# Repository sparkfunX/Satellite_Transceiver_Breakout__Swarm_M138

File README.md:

# Satellite Transceiver Breakout - Swarm M138

[*SparkFun Satellite Transceiver Kit - Swarm M138*](https://www.sparkfun.com/products/21287)

A breakout for the Swarm M138 satellite transceiver.

This breakout allows you to power and communicate with the Swarm M138 using USB 3 or USB-C, or breakout pins.

We've written a Python3 PyQt5 GUI to let you communicate with the modem. You will find it in its own dedicated repo:
- [**SparkFun Swarm M138 GUI**](https://github.com/sparkfun/SparkFun_Swarm_M138_GUI)

You will find the modem manual in the [**Documents**](./Documents) folder. It contains the full list of modem commands and messages.

You can also integrate the satellite transceiver directly into your project; the breakout pads can be used to provide power and access the 3.3V UART TX and RX signals.

Open the two split jumper pads on the bottom of the PCB first, located between the TXO/CH340_RXI and RXI/CH340_TXO pads. Then connect:
* GND to GND on your Arduino board
* VIN to 5V/V_USB on your Arduino board
* TXO to RX on your Arduino board (3.3V only!)
* RXI to TX on your Arduino board (3.3V only!)

Our [Swarm Satellite Arduino Library](https://github.com/sparkfun/SparkFun_Swarm_Satellite_Arduino_Library) makes communicating with the modem really easy.

## Repository Contents

- [**/Hardware**](./Hardware) - contains the Eagle PCB, SCH and LBR design files
- [**/Documents**](./Documents) - contains the datasheet etc. for the Swarm M138
- [**LICENSE.md**](./LICENSE.md) - contains the licence information

<br>

- [**SparkFun Swarm M138 GUI**](https://github.com/sparkfun/SparkFun_Swarm_M138_GUI) - dedicated repo for the Swarm M138 GUI

## Product Versions

- [KIT-21287](https://www.sparkfun.com/products/21287) - SparkFun Satellite Transceiver Kit - Swarm M138
- [SPX-19236](https://www.sparkfun.com/products/19236) - Original SparkX version

## License Information

This product is _**open source**_!

Please review the LICENSE.md file for license information.

If you have any questions or concerns on licensing, please contact technical support on our [SparkFun forums](https://forum.sparkfun.com/viewforum.php?f=123).

Distributed as-is; no warranty is given.

- Your friends at SparkFun.

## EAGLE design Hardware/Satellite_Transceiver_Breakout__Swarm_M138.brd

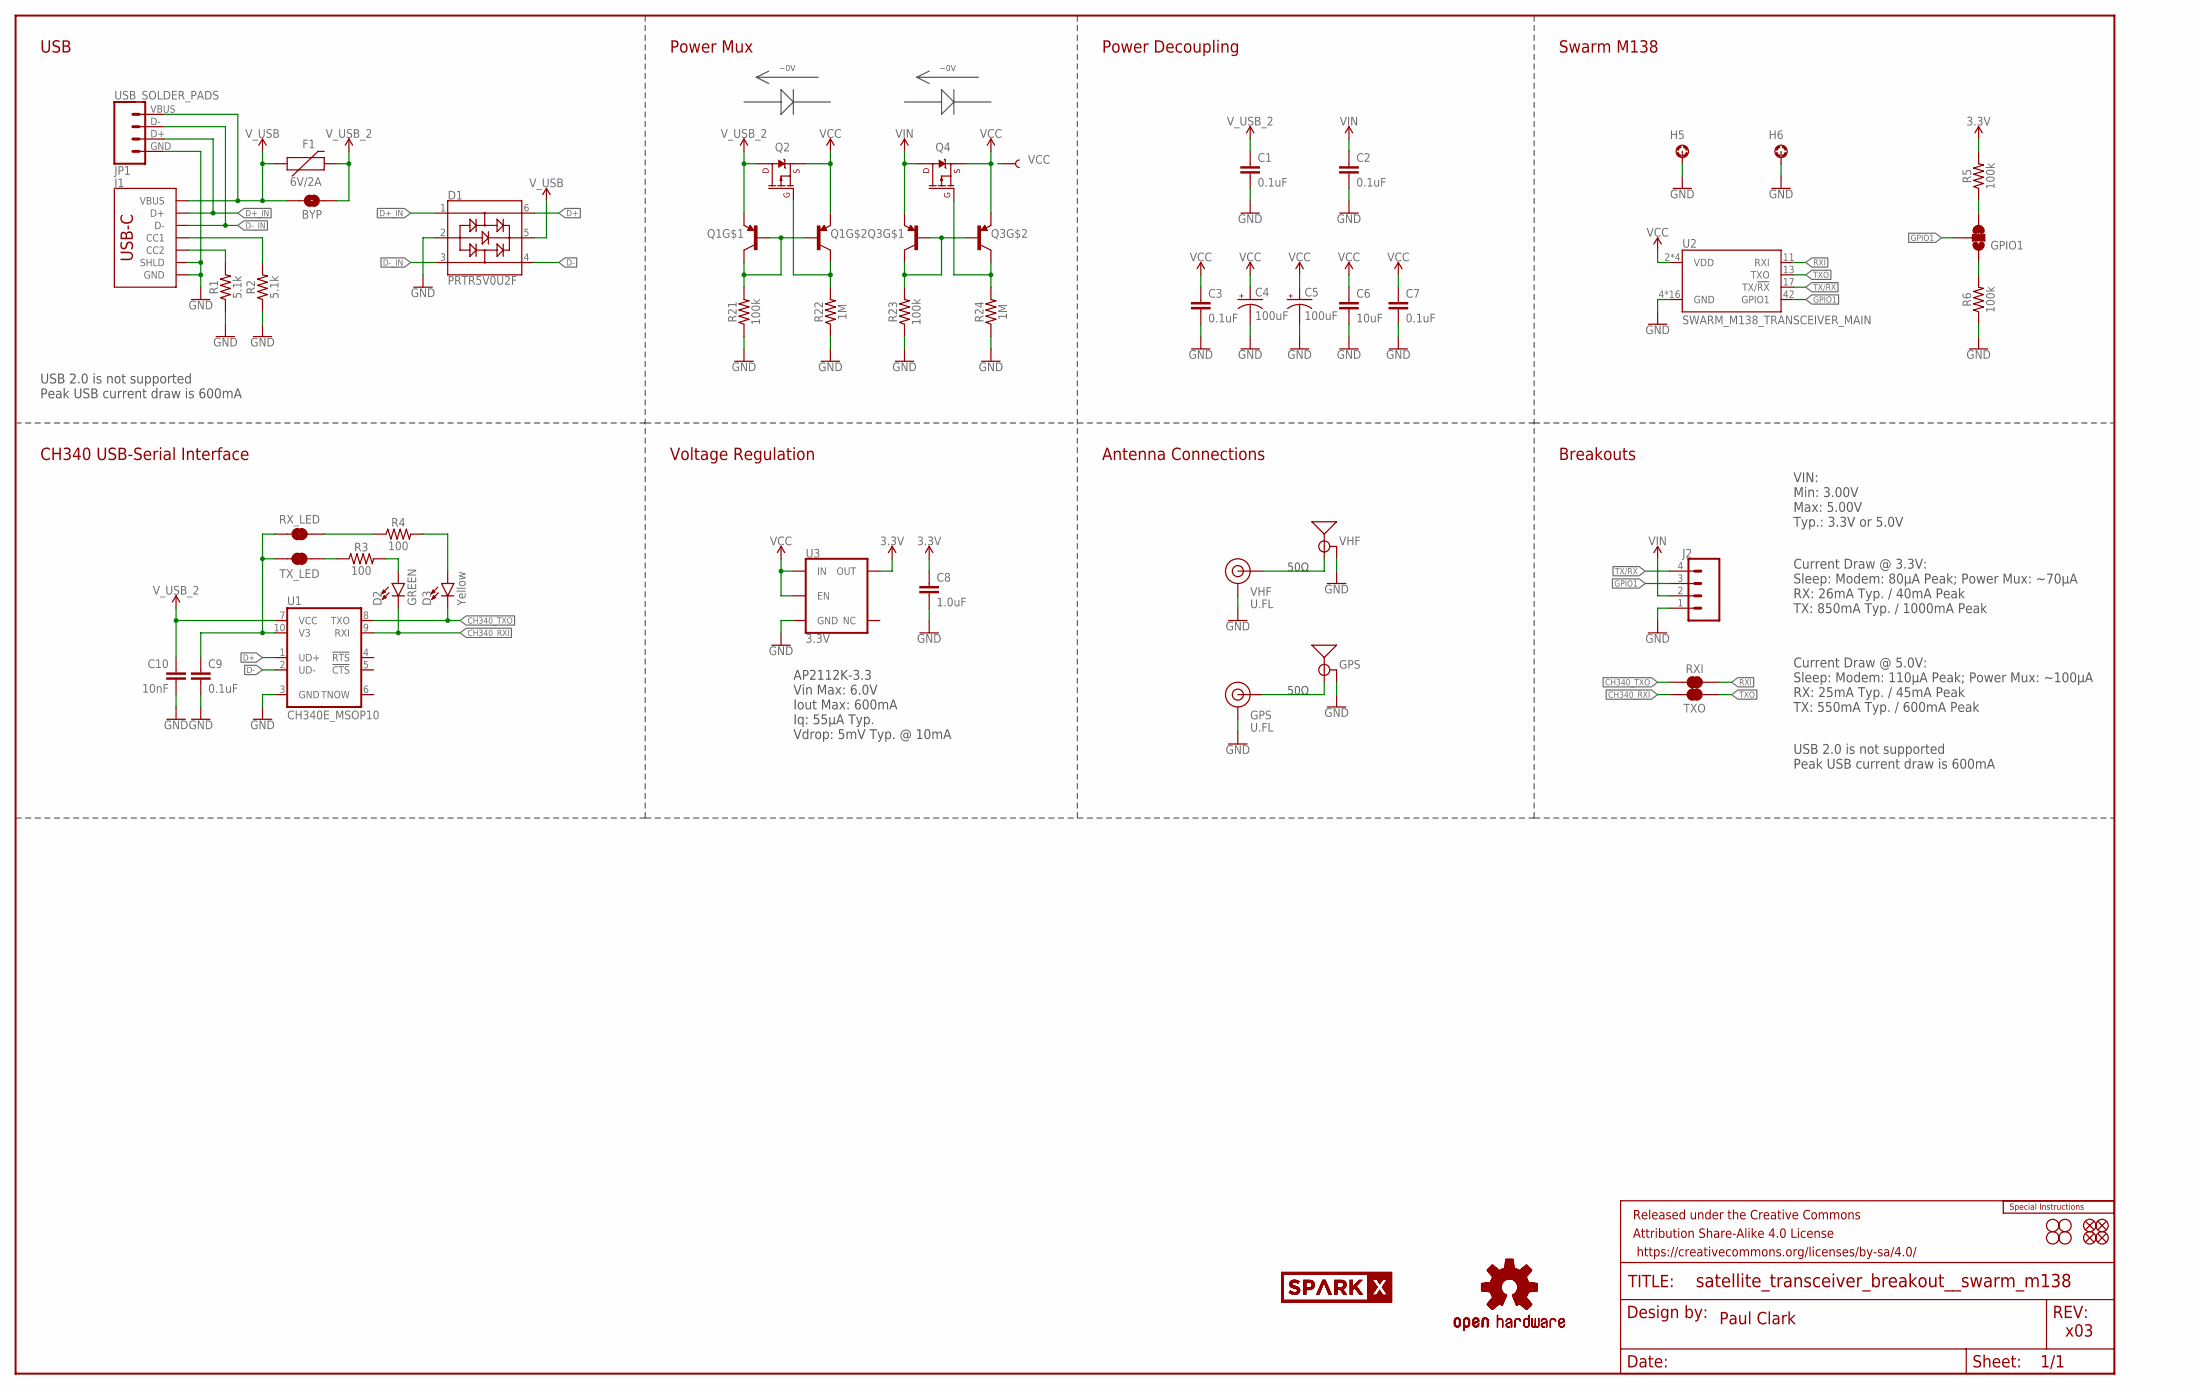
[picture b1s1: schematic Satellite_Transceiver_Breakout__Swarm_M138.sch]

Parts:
BYP: JUMPER-SMT_2_NO_SILK; SMT-JUMPER_2_NO_SILK
C1, C2, C3, C7, C9: 0.1uF; 0603
C4, C5: 100uF; PANASONIC_D
C6: 10uF; 0603
C8: 1.0uF; 0603
C10: 10nF; 0603
D1: PRTR5V0U2F; SOT886
D2: GREEN; LED-0603
D3: Yellow; LED-0603
E1: VHF; SMA-EDGE
E2: GPS; SMA-EDGE
F1: 6V/2A; 1210
FD1, FD2, FD3, FD4: FIDUCIAL1X2; FIDUCIAL-1X2
FRAME1: FRAME-LEDGER; CREATIVE_COMMONS
GPIO1: JUMPER-SMT_3_1-NC_TRACE_SILK; SMT-JUMPER_3_1-NC_TRACE_SILK
GPS: U.FL
H1, H2, H3, H4: STAND-OFF
H5, H6: STAND-OFF-REFLOW-M2.5_1.5MM_TALL; STAND-OFF-REFLOW-M2.5
J1: USB_C_2-LAYER_PADS; USB-C-16P-2LAYER-PADS
J2: CONN_041X04_NO_SILK; 1X04_NO_SILK
JP1: USB_SOLDER_PADS; USB-SOLDER-PADS
LOGO1: SPECIAL_INSTRUCTIONS-ORDERING; ORDERING_INSTRUCTIONS
LOGO2, LOGO3: OSHW-LOGOM; OSHW-LOGO-M
Q1, Q3: TRANS_PNP_DUALSOT-363; SOT363_PHILIPS
Q2, Q4: 20V/4.2A/52mΩ/1.4W; SOT23-3
R1, R2: 5.1k; 0603
R3, R4: 100; 0603
R5, R6, R21, R23: 100k; 0603
R22, R24: 1M; 0603
RXI: JUMPER-COMBO_2_NC_TRACE; COMBO-JUMPER_2_NC_TRACE
RX_LED: JUMPER-SMT_2_NC_TRACE_SILK; SMT-JUMPER_2_NC_TRACE_SILK
TXO: JUMPER-COMBO_2_NC_TRACE; COMBO-JUMPER_2_NC_TRACE
TX_LED: JUMPER-SMT_2_NC_TRACE_SILK; SMT-JUMPER_2_NC_TRACE_SILK
U1: CH340E_MSOP10; MSOP10
U2: SWARM_M138_TRANSCEIVER_MAIN; M.2-SWARM-M138-A
U3: 3.3V; SOT23-5
U$1, U$2: SPARKX-LOGO5; SPARKX-LARGE
VCC: TEST-POINT3X5; PAD.03X.05
VHF: U.FL

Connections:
3.3V: C8.1, R5.2, U3.5 (OUT)
CH340_RXI: D2.C, TXO.2, TXO.4 (2), U1.9 (RXI)
CH340_TXO: D3.C, RXI.1, RXI.3 (1), U1.8 (TXO)
D+: D1.6, U1.1 (UD+)
D+_IN: D1.1, J1.A6 (D+), J1.B6 (D+), JP1.D+ (3)
D-: D1.4, U1.2 (UD-)
D-_IN: D1.3, J1.A7 (D-), J1.B7 (D-), JP1.D- (2)
GND: C1.2, C2.2, C3.2, C4.-, C5.-, C6.2, C7.2, C8.2, C9.2, C10.2, D1.2, E1.GND@0 (GND), E1.GND@1 (GND), E1.GND@2 (GND), E1.GND@3 (GND), E2.GND@0 (GND), E2.GND@1 (GND), E2.GND@2 (GND), E2.GND@3 (GND), GPS.1 (GND), GPS.2 (GND), H5.1, H6.1, J1.GND, J1.GND2 (GND), J1.SHLD1 (SHLD), J1.SHLD2 (SHLD), J1.SHLD3 (SHLD), J1.SHLD4 (SHLD), J2.1, JP1.GND (4), R1.1, R2.1, R6.1, R21.1, R22.1, R23.1, R24.1, U1.3 (GND), U2.4 (GND), U2.9 (GND), U2.15 (GND), U2.18 (GND), U2.21 (GND), U2.26 (GND), U2.27 (GND), U2.29 (GND), U2.34 (GND), U2.35 (GND), U2.37 (GND), U2.40 (GND), U2.43 (GND), U2.50 (GND), U2.A1 (GND), U2.A2 (GND), U3.2 (GND), VHF.1 (GND), VHF.2 (GND)
GPIO1: GPIO1.2, J2.3, U2.42 (GPIO1)
GPS: E2.SIG (SIGNAL), GPS.FEED (SIGNAL)
unnamed: J1.B5 (CC2), R1.2
unnamed: J1.A5 (CC1), R2.2
unnamed: Q1.2 (B), Q1.5 (B), Q1.6 (C), R21.2
unnamed: C9.1, RX_LED.1, TX_LED.2, U1.10 (V3)
unnamed: R4.1, RX_LED.2
unnamed: D2.A, R3.2
unnamed: D3.A, R4.2
unnamed: R3.1, TX_LED.1
unnamed: Q1.3 (C), Q2.1 (G), R22.2
unnamed: GPIO1.3, R5.1
unnamed: Q3.2 (B), Q3.5 (B), Q3.6 (C), R23.2
unnamed: GPIO1.1, R6.2
unnamed: Q3.3 (C), Q4.1 (G), R24.2
RXI: RXI.2, RXI.4 (2), U2.11 (RXI)
TX/!RX!: J2.4, U2.17 (TX/!RX!)
TXO: TXO.1, TXO.3 (1), U2.13 (TXO)
VCC: C3.1, C4.+, C5.+, C6.1, C7.1, Q1.4 (E), Q2.2 (S), Q3.4 (E), Q4.2 (S), U2.2 (VDD), U2.39 (VDD), U2.41 (VDD), U2.52 (VDD), U3.1 (IN), U3.3 (EN), VCC.1
VHF: E1.SIG (SIGNAL), VHF.FEED (SIGNAL)
VIN: C2.1, J2.2, Q3.1 (E), Q4.3 (D)
V_USB: BYP.2, D1.5, F1.1, J1.VBUS1 (VBUS), J1.VBUS2 (VBUS), JP1.VBUS (1)
V_USB_2: BYP.1, C1.1, C10.1, F1.2, Q1.1 (E), Q2.3 (D), U1.7 (VCC)

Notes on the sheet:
x03
Paul Clark
USB
Power Mux
~0V
Power Decoupling
CH340 USB-Serial Interface
Swarm M138
Antenna Connections
50Ω
Breakouts
VIN: Min: 3.00V Max: 5.00V Typ.: 3.3V or 5.0V
Current Draw @ 3.3V: Sleep: Modem: 80µA Peak; Power Mux: ~70µA RX: 26mA Typ. / 40mA Peak TX: 850mA Typ. / 1000mA Peak
Current Draw @ 5.0V: Sleep: Modem: 110µA Peak; Power Mux: ~100µA RX: 25mA Typ. / 45mA Peak TX: 550mA Typ. / 600mA Peak
USB 2.0 is not supported Peak USB current draw is 600mA
Voltage Regulation
AP2112K-3.3 Vin Max: 6.0V Iout Max: 600mA Iq: 55µA Typ. Vdrop: 5mV Typ. @ 10mA

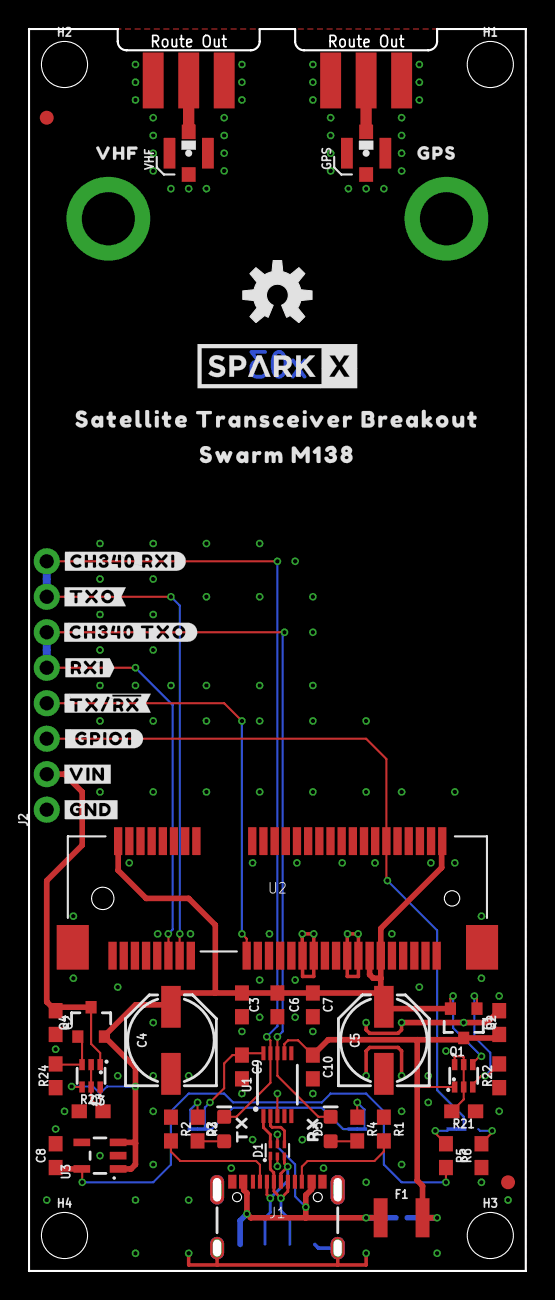
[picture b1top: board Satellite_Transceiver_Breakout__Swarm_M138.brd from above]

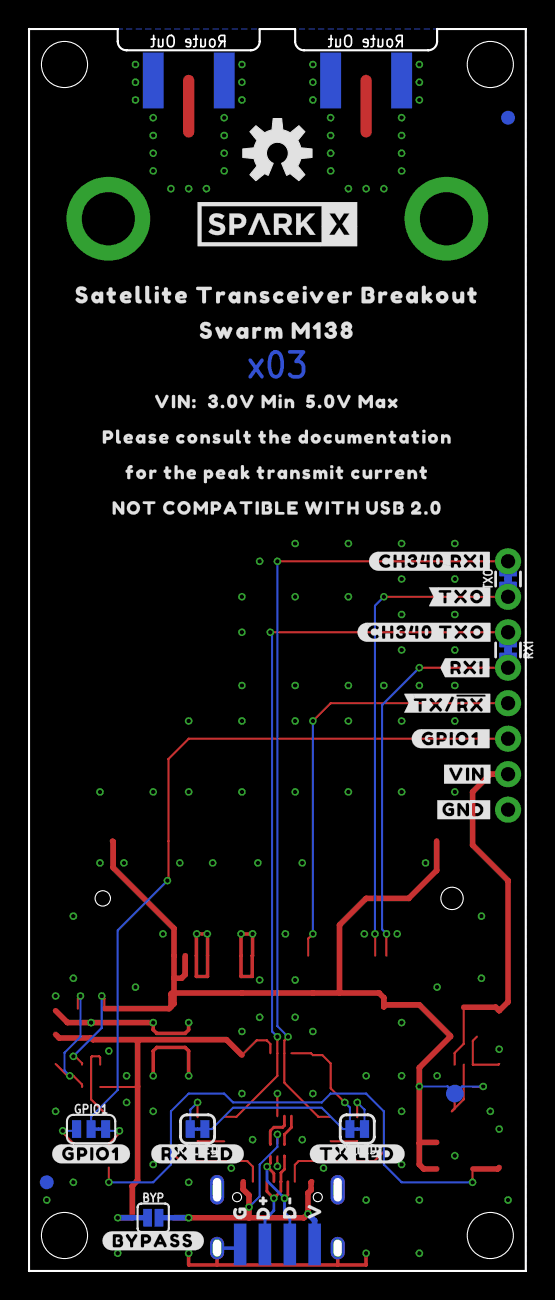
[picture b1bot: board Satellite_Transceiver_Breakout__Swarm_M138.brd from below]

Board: 2 copper layers, 35.1 x 88.5 mm, 97 parts (34 on the bottom side), 31 nets.

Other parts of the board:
U$3: VHF0
U$4: GPS0
U$5: VIN#__3#0V_MIN__5#0V_MAX0
U$6: PLEASE_CONSULT_THE_DOCUMENTATION0
U$7: #CH340_RXI#0
U$8: #CH340_RXI#341
U$9: #TXO#341
U$10: #TXO#342
U$11: #CH340_TXO#0
U$12: #CH340_TXO#341
U$13: #RXI#0
U$14: #RXI#1
U$15: #TX##RX##1
U$16: #TX##RX##0
U$17: #GPIO1_#2
U$18: V0
U$19: #GPIO1#0
U$20: #_GPIO1#2
U$21, U$22: #VIN#0
U$23, U$24: #GND#0
U$25: TX0
U$26: RX0
U$27: #TX_LED#0
U$28: #RX_LED#0
U$29: #BYPASS#0
U$30: G3
U$31: FOR_THE_PEAK_TRANSMIT_CURRENT1
U$32: NOT_COMPATIBLE_WITH_USB_2#02
U$34, U$39: SATELLITE_TRANSCEIVER_BREAKOUT0
U$36: D#2
U$37: D#1
U$40, U$41: SWARM_M1381

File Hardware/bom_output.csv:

Qty, PROD_ID, Names, Value, Package
5, CAP-08604, C1; C2; C3; C7; C9, 0.1uF, 0603
2, CAP-12547, C4; C5, 100uF, PANASONIC_D
1, CAP-11015, C6, 10uF, 0603
1, CAP-13930, C8, 1.0uF, 0603
1, CAP-00867, C10, 10nF, 0603
1, DIO-14084, D1, PRTR5V0U2F, SOT886
1, DIO-00821, D2, GREEN, LED-0603
1, DIO-09003, D3, Yellow, LED-0603
1, CONN-08289, E1, VHF, SMA-EDGE
1, CONN-08289, E2, GPS, SMA-EDGE
1, RES-14313, F1, 6V/2A, 1210
2, CONN-09193, GPS; VHF, U.FL, U.FL
2, HW-16629, H5; H6, STAND-OFF-REFLOW-M2.5_1.5MM_TALL, STAND-OFF-REFLOW-M2.5
1, CONN-14122, J1, , USB-C-16P-2LAYER-PADS
1, CONN-09696, J2, , 1X04_NO_SILK
2, TRANS-14386, Q1; Q3, , SOT363_PHILIPS
2, TRANS-14388, Q2; Q4, 20V/4.2A/52mΩ/1.4W, SOT23-3
2, RES-12083, R1; R2, 5.1k, 0603
2, RES-07863, R3; R4, 100, 0603
4, RES-07828, R5; R6; R21; R23, 100k, 0603
2, RES-07868, R22; R24, 1M, 0603
1, IC-14135, U1, CH340E_MSOP10, MSOP10
1, CONN-16558, U2, SWARM_M138_TRANSCEIVER_MAIN, M.2-SWARM-M138-A
1, VREG-12457, U3, 3.3V, SOT23-5

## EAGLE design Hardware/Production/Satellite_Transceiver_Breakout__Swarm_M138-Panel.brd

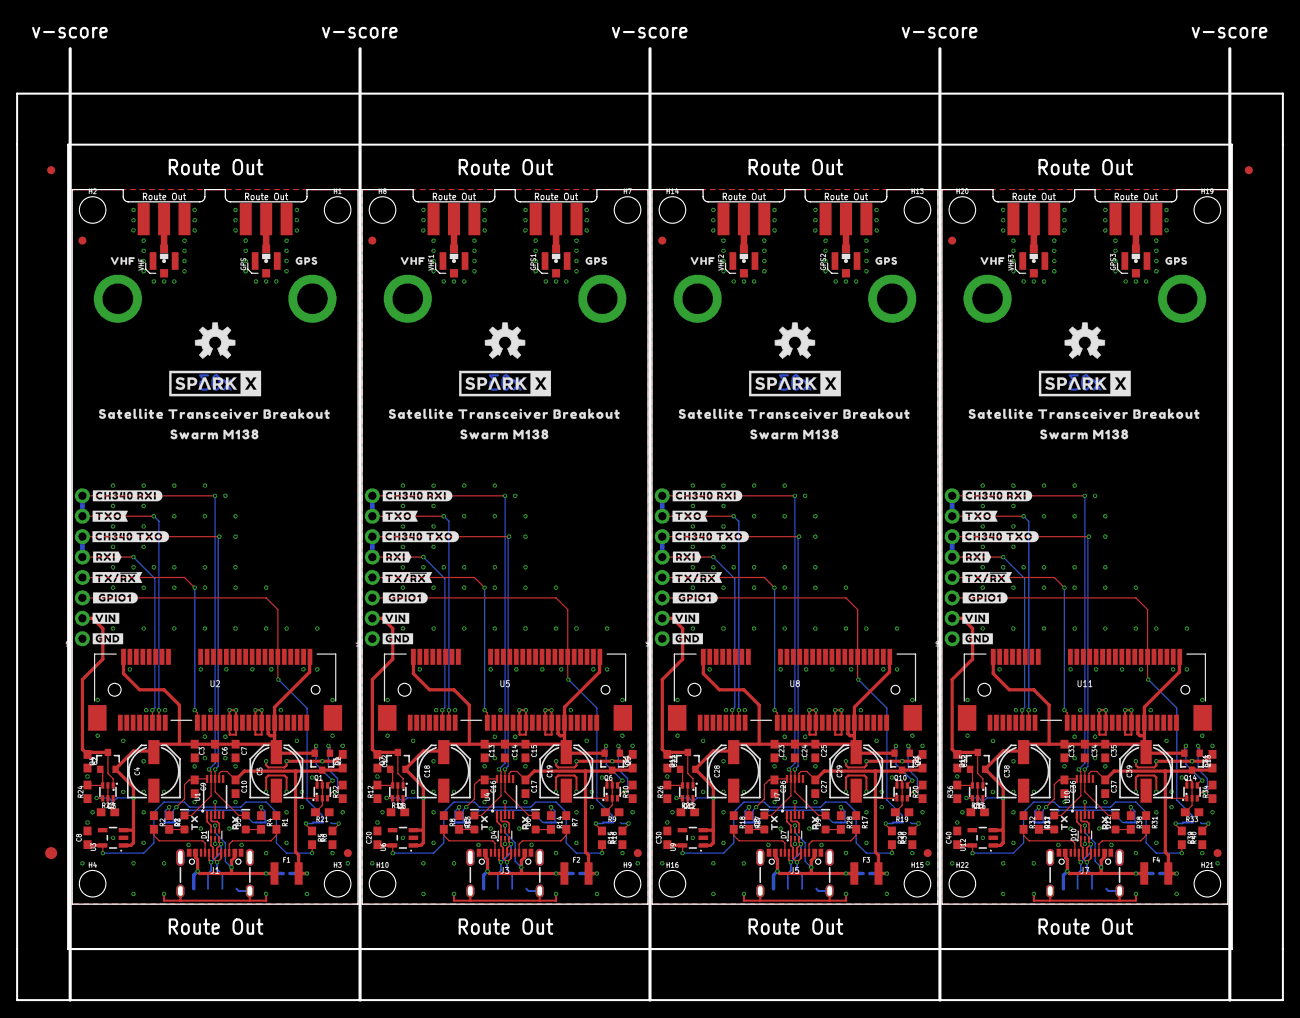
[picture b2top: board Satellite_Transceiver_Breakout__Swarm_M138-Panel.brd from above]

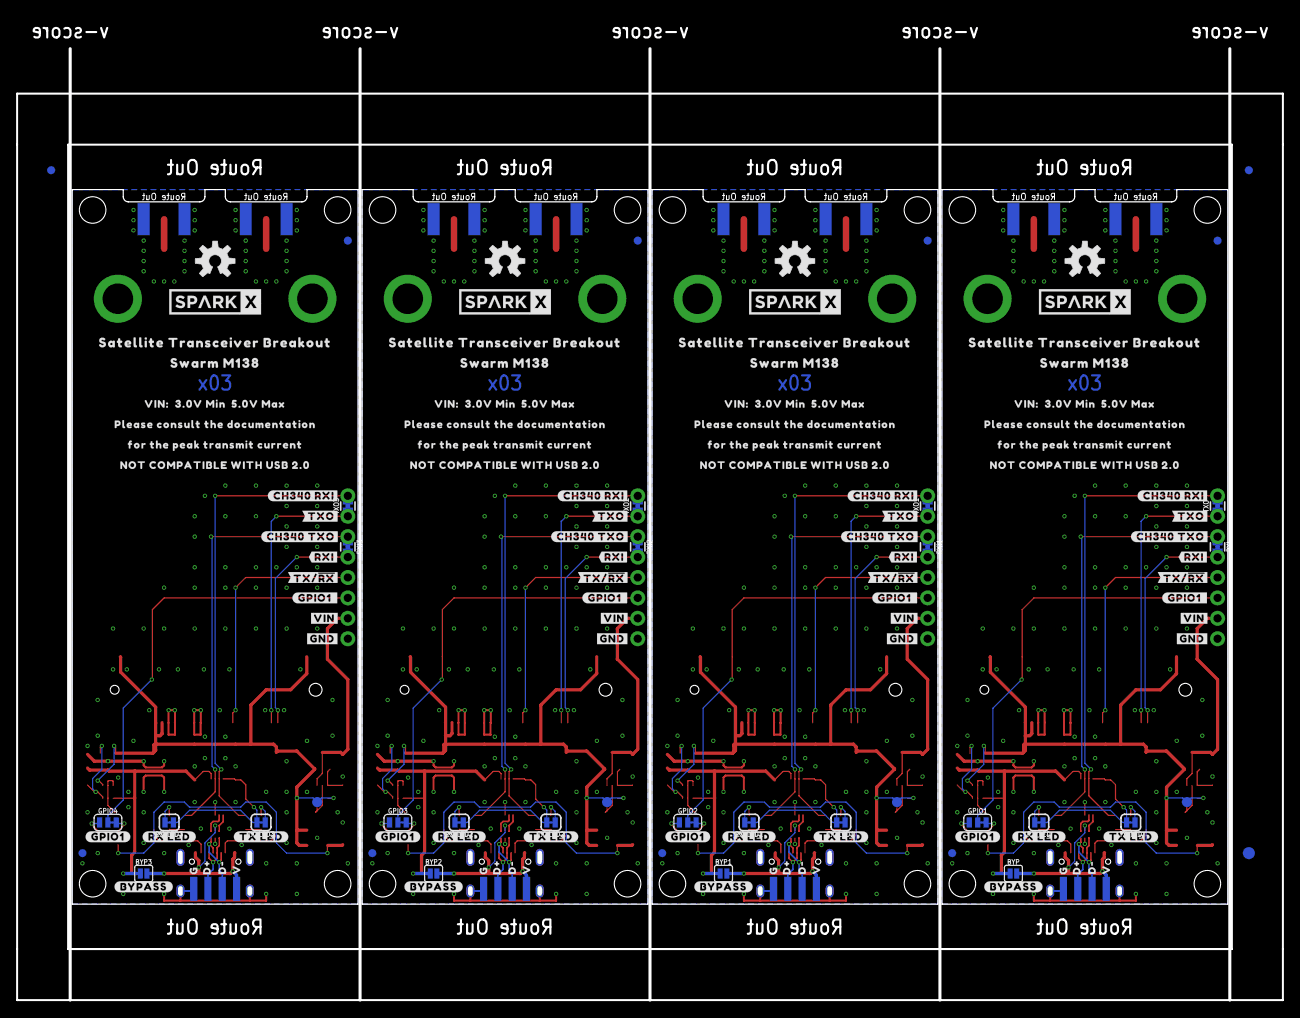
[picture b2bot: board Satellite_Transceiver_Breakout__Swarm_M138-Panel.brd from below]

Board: 2 copper layers, 157.1 x 122.0 mm, 386 parts (139 on the bottom side), 124 nets.

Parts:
BYP, BYP1, BYP2, BYP3: JUMPER-SMT_2_NO_SILK; SMT-JUMPER_2_NO_SILK
C1, C2, C3, C7, C9, C11, C12, C13, C15, C16, C21, C22, C23, C25, C26, C31, C32, C33, C35, C36: 0.1uF; 0603
C4, C5, C18, C19, C28, C29, C38, C39: 100uF; PANASONIC_D
C6, C14, C24, C34: 10uF; 0603
C8, C20, C30, C40: 1.0uF; 0603
C10, C17, C27, C37: 10nF; 0603
D1, D4, D7, D10: PRTR5V0U2F; SOT886
D2, D5, D8, D11: GREEN; LED-0603
D3, D6, D9, D12: Yellow; LED-0603
E1, E3, E5, E7: VHF; SMA-EDGE
E2, E4, E6, E8: GPS; SMA-EDGE
E$1, E$2, E$3, E$4: FIDUCIAL-1X2
E$5, E$6: FIDUCIAL-1.5X3
F1, F2, F3, F4: 6V/2A; 1210
FD1, FD2, FD3, FD4, FD5, FD6, FD7, FD8, FD9, FD10, FD11, FD12, FD13, FD14, FD15, FD16: FIDUCIAL1X2; FIDUCIAL-1X2
GPIO1, GPIO2, GPIO3, GPIO4: JUMPER-SMT_3_1-NC_TRACE_SILK; SMT-JUMPER_3_1-NC_TRACE_SILK
GPS, GPS1, GPS2, GPS3: U.FL
H1, H2, H3, H4, H7, H8, H9, H10, H13, H14, H15, H16, H19, H20, H21, H22: STAND-OFF
H5, H6, H11, H12, H17, H18, H23, H24: STAND-OFF-REFLOW-M2.5_1.5MM_TALL; STAND-OFF-REFLOW-M2.5
J1, J3, J5, J7: USB-C-16P-2LAYER-PADS
J2, J4, J6, J8: 1X04_NO_SILK
JP1, JP2, JP3, JP4: USB_SOLDER_PADS; USB-SOLDER-PADS
LOGO1, LOGO2, LOGO3, LOGO4, LOGO5, LOGO6, LOGO7, LOGO8: OSHW-LOGOM; OSHW-LOGO-M
Q1, Q3, Q6, Q8, Q10, Q12, Q14, Q16: SOT363_PHILIPS
Q2, Q4, Q5, Q7, Q9, Q11, Q13, Q15: 20V/4.2A/52mΩ/1.4W; SOT23-3
R1, R2, R7, R8, R17, R18, R31, R32: 5.1k; 0603
R3, R4, R13, R14, R27, R28, R37, R38: 100; 0603
R5, R6, R9, R11, R15, R16, R19, R21, R23, R25, R29, R30, R33, R35, R39, R40: 100k; 0603
R10, R12, R20, R22, R24, R26, R34, R36: 1M; 0603
RXI, RXI1, RXI2, RXI3: JUMPER-COMBO_2_NC_TRACE; COMBO-JUMPER_2_NC_TRACE
RX_LED, RX_LED1, RX_LED2, RX_LED3: JUMPER-SMT_2_NC_TRACE_SILK; SMT-JUMPER_2_NC_TRACE_SILK
TXO, TXO1, TXO2, TXO3: JUMPER-COMBO_2_NC_TRACE; COMBO-JUMPER_2_NC_TRACE
TX_LED, TX_LED1, TX_LED2, TX_LED3: JUMPER-SMT_2_NC_TRACE_SILK; SMT-JUMPER_2_NC_TRACE_SILK
U1, U4, U7, U10: CH340E_MSOP10; MSOP10
U2, U5, U8, U11: SWARM_M138_TRANSCEIVER_MAIN; M.2-SWARM-M138-A
U3, U6, U9, U12: 3.3V; SOT23-5
U$1, U$2, U$33, U$35, U$77, U$78, U$115, U$116: SPARKX-LOGO5; SPARKX-LARGE
U$3, U$38, U$79, U$117: VHF0
U$4, U$42, U$80, U$118: GPS0
U$5, U$76, U$114, U$152: VIN#__3#0V_MIN__5#0V_MAX0
U$6, U$73, U$111, U$149: PLEASE_CONSULT_THE_DOCUMENTATION0
U$7, U$52, U$90, U$128: #CH340_RXI#0
U$8, U$53, U$91, U$129: #CH340_RXI#341
U$9, U$54, U$92, U$130: #TXO#341
U$10, U$55, U$93, U$131: #TXO#342
U$11, U$56, U$94, U$132: #CH340_TXO#0
U$12, U$57, U$95, U$133: #CH340_TXO#341
U$13, U$58, U$96, U$134: #RXI#0
U$14, U$59, U$97, U$135: #RXI#1
U$15, U$61, U$99, U$137: #TX##RX##1
U$16, U$60, U$98, U$136: #TX##RX##0
U$17, U$63, U$101, U$139: #GPIO1_#2
U$18, U$65, U$103, U$141: V0
U$19, U$62, U$100, U$138: #GPIO1#0
U$20, U$64, U$102, U$140: #_GPIO1#2
U$21, U$22, U$43, U$44, U$81, U$82, U$119, U$120: #VIN#0
U$23, U$24, U$45, U$46, U$83, U$84, U$121, U$122: #GND#0
U$25, U$47, U$85, U$123: TX0
U$26, U$48, U$86, U$124: RX0
U$27, U$49, U$87, U$125: #TX_LED#0
U$28, U$50, U$88, U$126: #RX_LED#0
U$29, U$51, U$89, U$127: #BYPASS#0
U$30, U$66, U$104, U$142: G3
U$31, U$74, U$112, U$150: FOR_THE_PEAK_TRANSMIT_CURRENT1
U$32, U$75, U$113, U$151: NOT_COMPATIBLE_WITH_USB_2#02
U$34, U$39, U$69, U$70, U$107, U$108, U$145, U$146: SATELLITE_TRANSCEIVER_BREAKOUT0
U$36, U$67, U$105, U$143: D#2
U$37, U$68, U$106, U$144: D#1
U$40, U$41, U$71, U$72, U$109, U$110, U$147, U$148: SWARM_M1381
VCC, VCC1, VCC2, VCC3: TEST-POINT3X5; PAD.03X.05
VHF, VHF1, VHF2, VHF3: U.FL

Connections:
3.3V: C8.1, R5.2, U3.5
3.3V1: C20.1, R15.2, U6.5
3.3V2: C30.1, R29.2, U9.5
3.3V3: C40.1, R39.2, U12.5
CH340_RXI: D2.C, TXO.2, TXO.4, U1.9
CH340_RXI1: D5.C, TXO1.2, TXO1.4, U4.9
CH340_RXI2: D8.C, TXO2.2, TXO2.4, U7.9
CH340_RXI3: D11.C, TXO3.2, TXO3.4, U10.9
CH340_TXO: D3.C, RXI.1, RXI.3, U1.8
CH340_TXO1: D6.C, RXI1.1, RXI1.3, U4.8
CH340_TXO2: D9.C, RXI2.1, RXI2.3, U7.8
CH340_TXO3: D12.C, RXI3.1, RXI3.3, U10.8
D+: D1.6, U1.1
D+1: D4.6, U4.1
D+2: D7.6, U7.1
D+3: D10.6, U10.1
D+_IN: D1.1, J1.A6, J1.B6, JP1.D+
D+_IN1: D4.1, J3.A6, J3.B6, JP2.D+
D+_IN2: D7.1, J5.A6, J5.B6, JP3.D+
D+_IN3: D10.1, J7.A6, J7.B6, JP4.D+
D-: D1.4, U1.2
D-1: D4.4, U4.2
D-2: D7.4, U7.2
D-3: D10.4, U10.2
D-_IN: D1.3, J1.A7, J1.B7, JP1.D-
D-_IN1: D4.3, J3.A7, J3.B7, JP2.D-
D-_IN2: D7.3, J5.A7, J5.B7, JP3.D-
D-_IN3: D10.3, J7.A7, J7.B7, JP4.D-
GND: C1.2, C2.2, C3.2, C4.-, C5.-, C6.2, C7.2, C8.2, C9.2, C10.2, D1.2, E1.GND@0, E1.GND@1, E1.GND@2, E1.GND@3, E2.GND@0, E2.GND@1, E2.GND@2, E2.GND@3, GPS.1, GPS.2, H5.1, H6.1, J1.GND, J1.GND2, J1.SHLD1, J1.SHLD2, J1.SHLD3, J1.SHLD4, J2.1, JP1.GND, R1.1, R2.1, R6.1, R21.1, R22.1, R23.1, R24.1, U1.3, U2.4, U2.9, U2.15, U2.18, U2.21, U2.26, U2.27, U2.29, U2.34, U2.35, U2.37, U2.40, U2.43, U2.50, U2.A1, U2.A2, U3.2, VHF.1, VHF.2
GND1: C11.2, C12.2, C13.2, C14.2, C15.2, C16.2, C17.2, C18.-, C19.-, C20.2, D4.2, E3.GND@0, E3.GND@1, E3.GND@2, E3.GND@3, E4.GND@0, E4.GND@1, E4.GND@2, E4.GND@3, GPS1.1, GPS1.2, H11.1, H12.1, J3.GND, J3.GND2, J3.SHLD1, J3.SHLD2, J3.SHLD3, J3.SHLD4, J4.1, JP2.GND, R7.1, R8.1, R9.1, R10.1, R11.1, R12.1, R16.1, U4.3, U5.4, U5.9, U5.15, U5.18, U5.21, U5.26, U5.27, U5.29, U5.34, U5.35, U5.37, U5.40, U5.43, U5.50, U5.A1, U5.A2, U6.2, VHF1.1, VHF1.2
GND2: C21.2, C22.2, C23.2, C24.2, C25.2, C26.2, C27.2, C28.-, C29.-, C30.2, D7.2, E5.GND@0, E5.GND@1, E5.GND@2, E5.GND@3, E6.GND@0, E6.GND@1, E6.GND@2, E6.GND@3, GPS2.1, GPS2.2, H17.1, H18.1, J5.GND, J5.GND2, J5.SHLD1, J5.SHLD2, J5.SHLD3, J5.SHLD4, J6.1, JP3.GND, R17.1, R18.1, R19.1, R20.1, R25.1, R26.1, R30.1, U7.3, U8.4, U8.9, U8.15, U8.18, U8.21, U8.26, U8.27, U8.29, U8.34, U8.35, U8.37, U8.40, U8.43, U8.50, U8.A1, U8.A2, U9.2, VHF2.1, VHF2.2
GND3: C31.2, C32.2, C33.2, C34.2, C35.2, C36.2, C37.2, C38.-, C39.-, C40.2, D10.2, E7.GND@0, E7.GND@1, E7.GND@2, E7.GND@3, E8.GND@0, E8.GND@1, E8.GND@2, E8.GND@3, GPS3.1, GPS3.2, H23.1, H24.1, J7.GND, J7.GND2, J7.SHLD1, J7.SHLD2, J7.SHLD3, J7.SHLD4, J8.1, JP4.GND, R31.1, R32.1, R33.1, R34.1, R35.1, R36.1, R40.1, U10.3, U11.4, U11.9, U11.15, U11.18, U11.21, U11.26, U11.27, U11.29, U11.34, U11.35, U11.37, U11.40, U11.43, U11.50, U11.A1, U11.A2, U12.2, VHF3.1, VHF3.2
GPIO1: GPIO1.2, J2.3, U2.42
GPIO2: GPIO2.2, J4.3, U5.42
GPIO3: GPIO3.2, J6.3, U8.42
GPIO4: GPIO4.2, J8.3, U11.42
GPS: E2.SIG, GPS.FEED
GPS1: E4.SIG, GPS1.FEED
GPS2: E6.SIG, GPS2.FEED
GPS3: E8.SIG, GPS3.FEED
unnamed: J3.B5, R7.2
unnamed: J1.B5, R1.2
unnamed: J1.A5, R2.2
unnamed: J3.A5, R8.2
unnamed: Q1.2, Q1.5, Q1.6, R21.2
unnamed: C9.1, RX_LED.1, TX_LED.2, U1.10
unnamed: R4.1, RX_LED.2
unnamed: Q6.2, Q6.5, Q6.6, R9.2
unnamed: D2.A, R3.2
unnamed: D3.A, R4.2
unnamed: Q5.1, Q6.3, R10.2
unnamed: R3.1, TX_LED.1
unnamed: Q1.3, Q2.1, R22.2
unnamed: GPIO1.3, R5.1
unnamed: Q3.2, Q3.5, Q3.6, R23.2
unnamed: GPIO1.1, R6.2
unnamed: Q8.2, Q8.5, Q8.6, R11.2
unnamed: Q7.1, Q8.3, R12.2
unnamed: C16.1, RX_LED1.1, TX_LED1.2, U4.10
unnamed: D5.A, R13.2
unnamed: D6.A, R14.2
unnamed: R14.1, RX_LED1.2
unnamed: R13.1, TX_LED1.1
unnamed: GPIO2.3, R15.1
unnamed: GPIO2.1, R16.2
unnamed: J5.B5, R17.2
unnamed: J5.A5, R18.2
unnamed: Q3.3, Q4.1, R24.2
unnamed: Q10.2, Q10.5, Q10.6, R19.2
unnamed: Q9.1, Q10.3, R20.2
unnamed: Q12.2, Q12.5, Q12.6, R25.2
unnamed: Q11.1, Q12.3, R26.2
unnamed: C26.1, RX_LED2.1, TX_LED2.2, U7.10
unnamed: D8.A, R27.2
unnamed: D9.A, R28.2
unnamed: R28.1, RX_LED2.2
unnamed: R27.1, TX_LED2.1
unnamed: GPIO3.3, R29.1
unnamed: GPIO3.1, R30.2
unnamed: J7.B5, R31.2
unnamed: J7.A5, R32.2
unnamed: Q14.2, Q14.5, Q14.6, R33.2
unnamed: Q13.1, Q14.3, R34.2
unnamed: Q16.2, Q16.5, Q16.6, R35.2
unnamed: Q15.1, Q16.3, R36.2
unnamed: C36.1, RX_LED3.1, TX_LED3.2, U10.10
unnamed: D11.A, R37.2
unnamed: D12.A, R38.2
unnamed: R38.1, RX_LED3.2
unnamed: R37.1, TX_LED3.1
unnamed: GPIO4.3, R39.1
unnamed: GPIO4.1, R40.2
RXI: RXI.2, RXI.4, U2.11
RXI1: RXI1.2, RXI1.4, U5.11
RXI2: RXI2.2, RXI2.4, U8.11
RXI3: RXI3.2, RXI3.4, U11.11
TX/!RX!: J2.4, U2.17
TX/!RX!1: J4.4, U5.17
TX/!RX!2: J6.4, U8.17
TX/!RX!3: J8.4, U11.17
TXO: TXO.1, TXO.3, U2.13
TXO1: TXO1.1, TXO1.3, U5.13
TXO2: TXO2.1, TXO2.3, U8.13
TXO3: TXO3.1, TXO3.3, U11.13
VCC: C3.1, C4.+, C5.+, C6.1, C7.1, Q1.4, Q2.2, Q3.4, Q4.2, U2.2, U2.39, U2.41, U2.52, U3.1, U3.3, VCC.1
VCC1: C13.1, C14.1, C15.1, C18.+, C19.+, Q5.2, Q6.4, Q7.2, Q8.4, U5.2, U5.39, U5.41, U5.52, U6.1, U6.3, VCC1.1
VCC2: C23.1, C24.1, C25.1, C28.+, C29.+, Q9.2, Q10.4, Q11.2, Q12.4, U8.2, U8.39, U8.41, U8.52, U9.1, U9.3, VCC2.1
VCC3: C33.1, C34.1, C35.1, C38.+, C39.+, Q13.2, Q14.4, Q15.2, Q16.4, U11.2, U11.39, U11.41, U11.52, U12.1, U12.3, VCC3.1
VHF: E1.SIG, VHF.FEED
VHF1: E3.SIG, VHF1.FEED
VHF2: E5.SIG, VHF2.FEED
VHF3: E7.SIG, VHF3.FEED
VIN: C2.1, J2.2, Q3.1, Q4.3
VIN1: C12.1, J4.2, Q7.3, Q8.1
VIN2: C22.1, J6.2, Q11.3, Q12.1
VIN3: C32.1, J8.2, Q15.3, Q16.1
V_USB: BYP.2, D1.5, F1.1, J1.VBUS1, J1.VBUS2, JP1.VBUS
V_USB1: BYP1.2, D4.5, F2.1, J3.VBUS1, J3.VBUS2, JP2.VBUS
V_USB2: BYP2.2, D7.5, F3.1, J5.VBUS1, J5.VBUS2, JP3.VBUS
V_USB3: BYP3.2, D10.5, F4.1, J7.VBUS1, J7.VBUS2, JP4.VBUS
V_USB_1: BYP1.1, C11.1, C17.1, F2.2, Q5.3, Q6.1, U4.7
V_USB_2: BYP.1, C1.1, C10.1, F1.2, Q1.1, Q2.3, U1.7
V_USB_3: BYP2.1, C21.1, C27.1, F3.2, Q9.3, Q10.1, U7.7
V_USB_4: BYP3.1, C31.1, C37.1, F4.2, Q13.3, Q14.1, U10.7

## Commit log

2022-03-10 Add the README and LICENSE
2022-03-10 Add Documents
2022-03-10 Add x02 Hardware
2022-03-13 Update NC jumper links
2022-03-15 Replace 3.3V Reg with AP2112K
2022-03-24 Add ignore. Add ground plate.
2022-03-25 Add revised ground plate
2022-03-25 Combining ground plate versions
2022-03-25 Adding gerbers
2022-04-22 Add Windows and RPi exe's
2022-04-22 Update product image
2022-05-18 Add Ground Plane dimensions
2022-05-20 Updates for x03 PCB - move standoffs by 0.6mm and add route-out gaps in panel
2022-08-02 Add BOM
2023-03-04 Add a link to the new GUI repo
2023-03-04 Update product links

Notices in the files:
parts and their libraries:
SparkFun-Aesthetics: Licensing: Creative Commons ShareAlike 4.0 International - https://creativecommons.org/licenses/by-sa/4.0
SparkFun-Aesthetics: Released under the Creative Commons Attribution Share-Alike 4.0 License
SparkFun-Aesthetics: https://creativecommons.org/licenses/by-sa/4.0
